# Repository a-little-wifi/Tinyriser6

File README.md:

# Tinyriser Hex (Tinyriser6)
Tinyriser for the Tiny6 and Tiny7 generation of Lenovo Tiny PCs
Same idea as [the original Tinyriser](https://github.com/a-little-wifi/Tinyriser), but for the next gen.  
Compatible with M90q gen 1 & 2, P340 and P350 Tiny (M70q and M80q don't have the riser slot populated)

## Features:

- PCIe x16 slot (8 lanes from CPU)
- M.2 M-key NVMe slot (4 lanes from PCH)
- USB 2.0 port
- Fan header
- Other random riser slot IO breakout (for science)
- Plug and play, no mainboard modification necessary

> front and back in 3D render  

> front and back in real life

This riser gives you access to the PCIe x8 link from the CPU and the PCIe x4 link from the PCH at the same time, in the form of a PCIe x16 (physical) slot and an M.2 M-key slot.  
Also has a USB 2.0 port because the riser slot has it so why not.  
It does not require any modification to the motherboard of the host machine, just plug and play.  

Using this riser, you can install a low profile PCIe card just as you can with the stock risers, and add an extra M.2 NVMe SSD in addition to the onboard ones. The SSD is tucked away near the front of the machine, plugged into a right angle M-key M.2 slot that holds the SSD firmly in place.  
M.2 2280 length SSDs might have some trouble fitting, especially in combination with longer PCIe cards as they run into the fan and speaker connector on the motherboard. I leave it up to the individual to judge what will be a good fit.  

I've successfully tested this design in P340 (Tiny6) and P350 (Tiny7) machines. Both PCIe links with all lanes as well as the USB port are fully functional in both of them.  

> riser installed in a P340 with PCIe card, SSD and USB cable attached

### Fan header:
The fan header has the same 3 modes as on the original Tinyriser:
- 12V no PWM
- 12V with PWM
- Voltage controlled speed

The last 2 modes require some kind of fan controller module plugged into the provided header. This has not been designed yet, but the possibility exists.

**Update: v1.1 now has a '5V no PWM' mode available as well, adding an extra jumper from the 5V rail instead of the 12V rail. This 5V rail is always on though, so the fan would be powered even when the system is turned off.**  
**Also be careful when soldering the 5V jumper, it's really close to a 12V pin from the PCIe slot.**

## Thank you

I want to say thank you to everyone for the kind words about my first riser design, I never expected it to reach so far and get so much interest. I originally made it just because I wanted to know if it would work and because I needed a riser for my M720q anyway (would you believe I don't own or have even ever seen a stock Lenovo Tiny5 riser?).  
The experience has had its ups and downs, it turned out I was nowhere near prepared to be handling sales, there's been a few people trying to take credit for my work, and life has been throwing one thing after the other at me, there've been many times I felt bad about it (sorry for the occasional blunt or delayed replies), but in the end I'm still glad I could put it out there and that people have been able to enjoy it. I've even had people reach out suggesting different riser versions and requesting assistance with making modified designs, that's what I love to see. I hope the same will go for this one.

So really, thank you to everyone who has expressed their appreciation for my work, and maybe even bought one from me directly during the short time that was possible. Your support really fills my little wifi heart with motivation to continue making my silly pieces of PCB art in my own way. I hope to keep delving into the depths of modern PC hardware architecture and to deliver more high quality designs with some soul of their own in the future.

This design is the result of everything I've learned from my experience with the original Tinyariser and more. It includes an improved edge connector design that better follows industry standards, a short-circuit discouragement pictogram, several hidden cats, silly puns and more magic.

### Made with ❤ and ✨ by Wifi. I poured my heart, soul and passion into this, I hope you love it too!

## Parts list: 
| part                    | model                     | link                                                                                             |
|-------------------------|---------------------------|--------------------------------------------------------------------------------------------------|
| PCIe slot               | UMAX 3183-10203P1T        | https://www.lcsc.com/product-detail/Card-Edge-Connectors_UMAX-3183-10203P1T_C404116.html         |
| Vertical M-key slot     | HOAUC HYCW19M-05NGFF-530B | https://www.lcsc.com/product-detail/C41430861.html                                               |
| Alt Vertical M-key slot | Lotes APCI0110-P001A      | (available on aliexpress)                                                                        |
| Screwpost               | YIYUAN SMTSOM340BTR       | https://www.lcsc.com/product-detail/Other-nuts_YIYUAN-SMTSOM340BTR_C5301786.html                 |
| USB port                | Jing 906-862A1118D10200   | https://www.lcsc.com/product-detail/C2763236.html (Warning: EasyEDA footprint pinout is reversed)|

## JLC PCB ordering details:

Please use the files from the v1 release, the main repo might be in the middle of version changes

You're welcome to place your own group orders if you know enough people who are interested in getting one of these risers, however please leave actual selling of this riser design to me and people I've specifically made agreements with.

### Order it in purple Ò̶̖͗̅Ŕ̵͈ ̴̠̬̝̚E̷̖̘̐́̿L̴̢͉̠̕͝S̵͖̺̰̋̀Ē̶̫̾ͅ

> Screenshot of the JLC PCB order settings used for Tinyriser6

# Attribution
If you distribute this design or use this design to create a derivative design, you must keep attribution to this original design, in addition to following the terms in the license

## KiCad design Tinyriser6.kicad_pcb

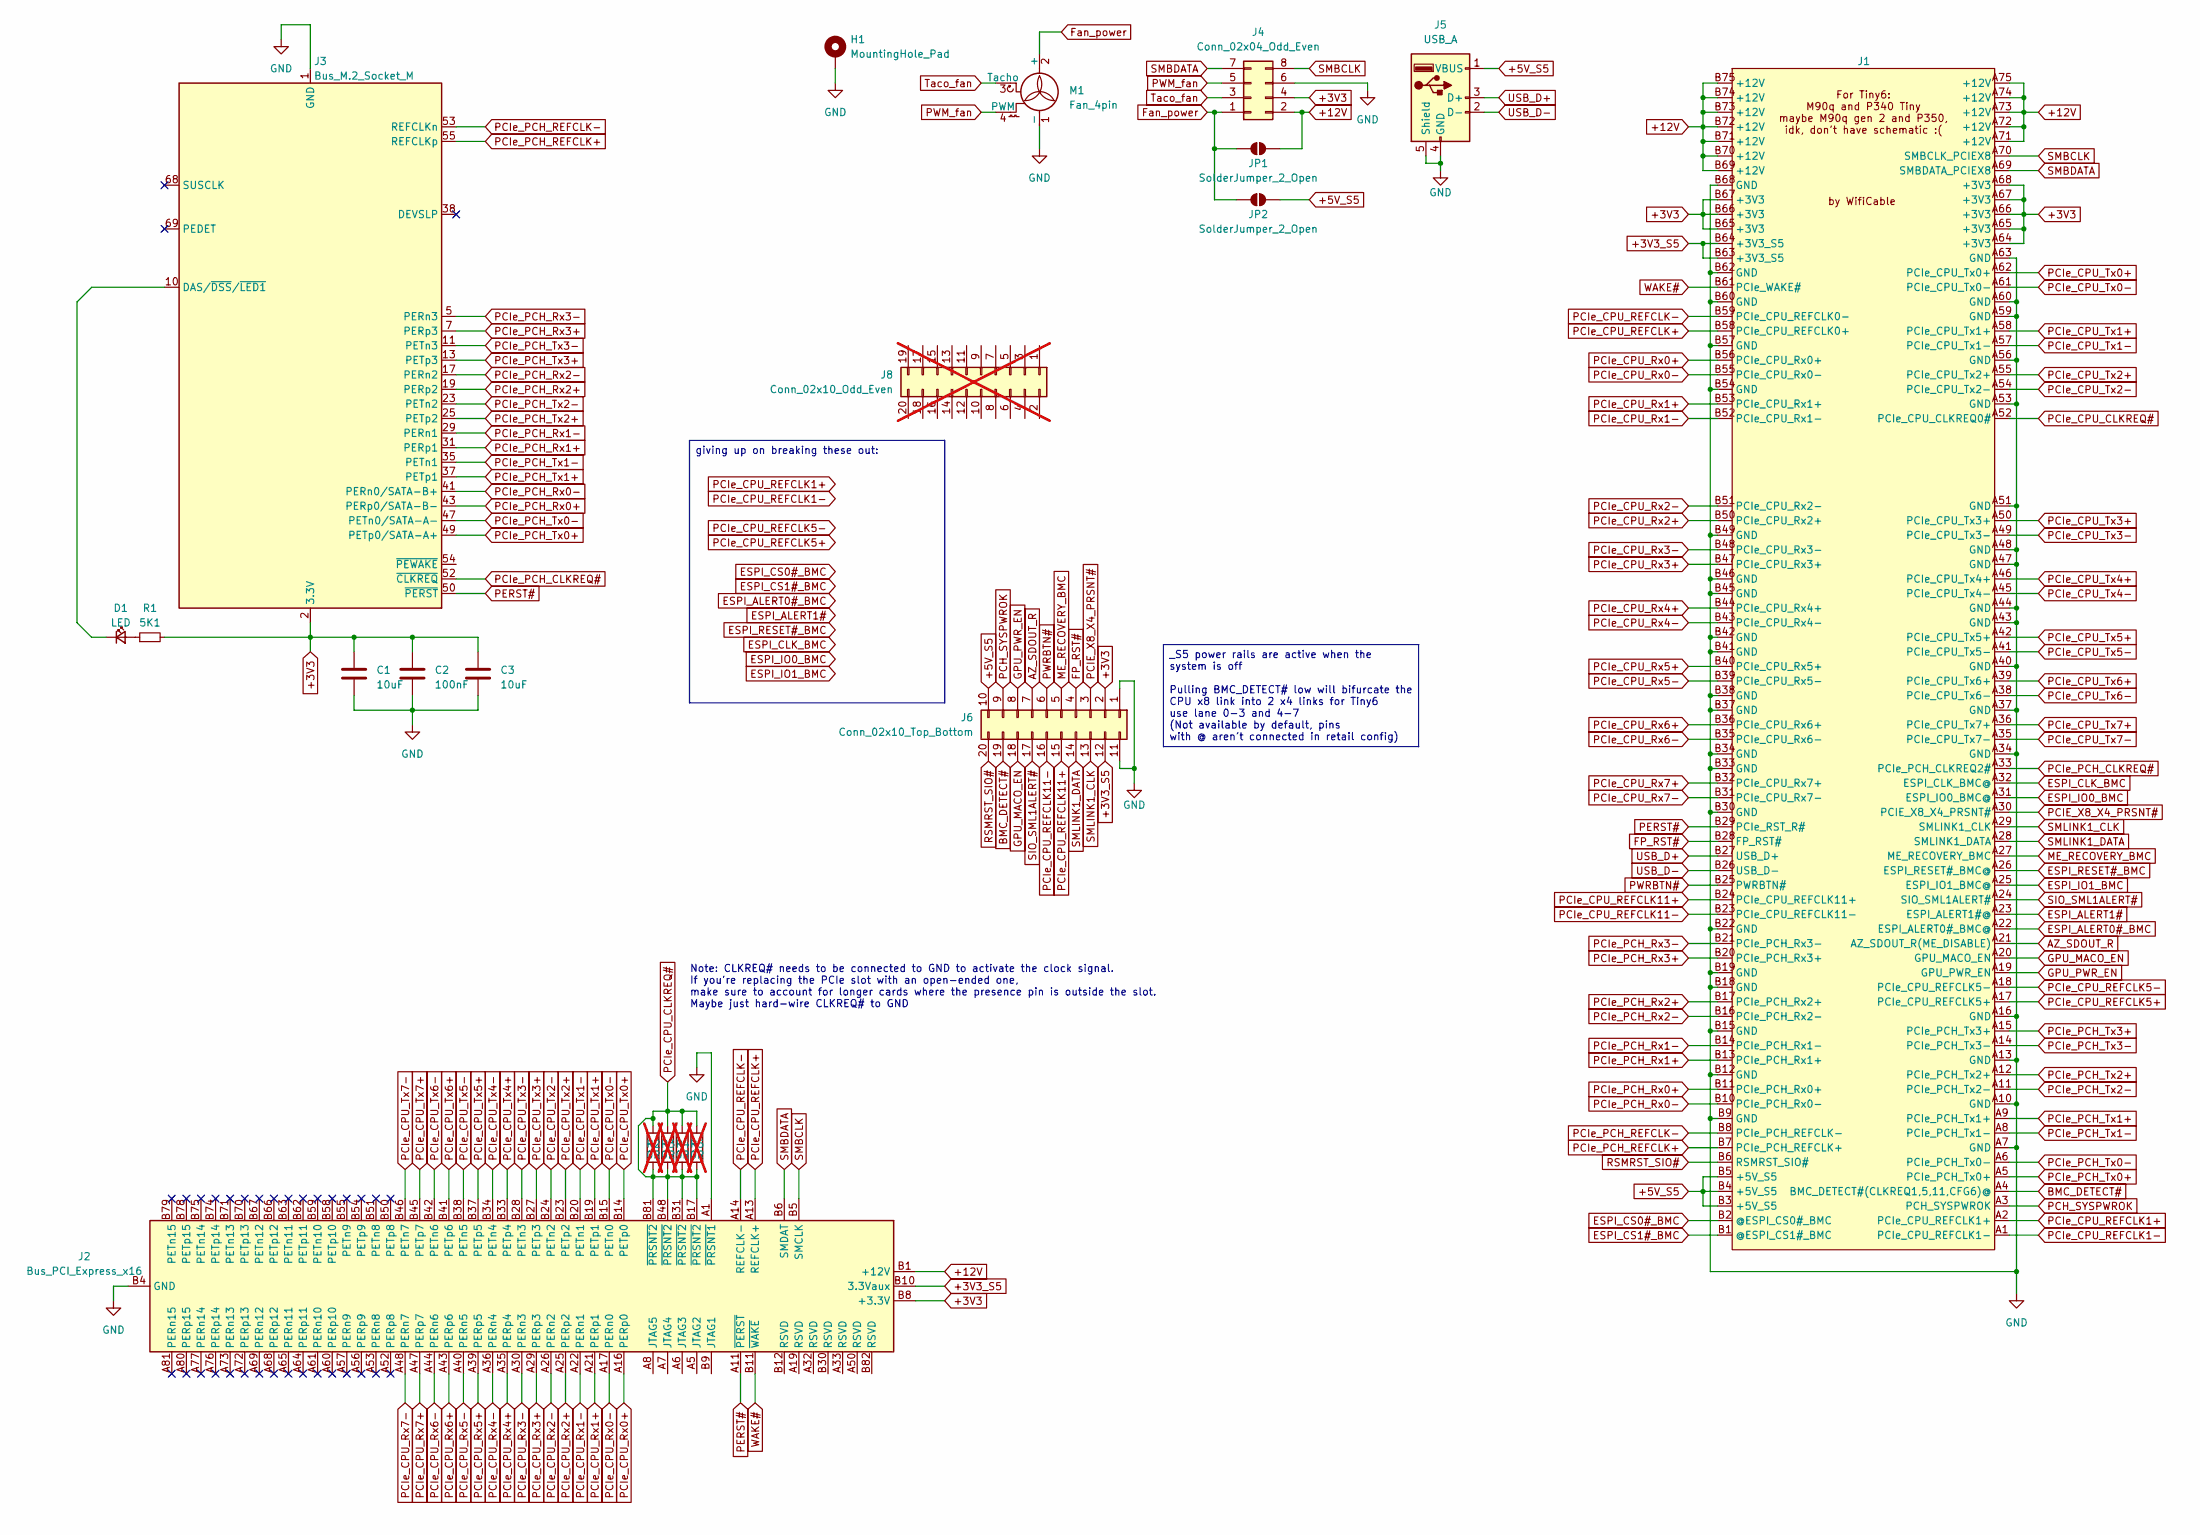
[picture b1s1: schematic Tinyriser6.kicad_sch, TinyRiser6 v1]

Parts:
C1, C3: 10uF; C_0603_1608Metric
C2: 100nF; C_0603_1608Metric
D1: LED; D_0603_1608Metric_Pad1.05x0.95mm_HandSolder
H1: MountingHole_Pad; MountingHole_4.3mm_M4_ISO7380_Pad_TopOnly
J1: TinyRiser6
J2: Bus_PCI_Express_x16; PCIe_x16_tht_smallholes
J3: Bus_M.2_Socket_M; M.2_NGFF_KeyM_H5.3_Vertical
J4: Conn_02x04_Odd_Even; PinSocket_2x04_P2.54mm_Horizontal
J5: USB_A; that-sideways-usb
J6: Conn_02x10_Top_Bottom; PinHeader_2x10_P2.54mm_Vertical
J8: Conn_02x10_Odd_Even; PinHeader_2x10_P2.54mm_Vertical; not fitted
JP1, JP2: SolderJumper_2_Open; SolderJumper-2_P1.3mm_Open_TrianglePad1.0x1.5mm
M1: Fan_4pin; PinHeader_1x04_P2.54mm_Horizontal
R1: 5K1; R_0603_1608Metric_Pad0.98x0.95mm_HandSolder
R2, R3, R4, R5: 0R; R_0603_1608Metric_Pad0.98x0.95mm_HandSolder; not fitted

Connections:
+3V3: C1.1, C2.1, C3.1, J1.A64 (+3V3), J1.A65 (+3V3), J1.A66 (+3V3), J1.A67 (+3V3), J1.A68 (+3V3), J1.B65 (+3V3), J1.B66 (+3V3), J1.B67 (+3V3), J2.A9 (+3.3V), J2.A10 (+3.3V), J2.B8 (+3.3V), J3.2 (3.3V), J3.4 (3.3V), J3.12 (3.3V), J3.14 (3.3V), J3.16 (3.3V), J3.18 (3.3V), J3.70 (3.3V), J3.72 (3.3V), J3.74 (3.3V), J4.4, J6.2, R1.2
+3V3_S5: J1.B63 (+3V3_S5), J1.B64 (+3V3_S5), J2.B10 (3.3Vaux), J6.12
+5V_S5: J1.B3 (+5V_S5), J1.B4 (+5V_S5), J1.B5 (+5V_S5), J5.1 (VBUS), J6.10, JP2.2 (B)
+12V: J1.A71 (+12V), J1.A72 (+12V), J1.A73 (+12V), J1.A74 (+12V), J1.A75 (+12V), J1.B69 (+12V), J1.B70 (+12V), J1.B71 (+12V), J1.B72 (+12V), J1.B73 (+12V), J1.B74 (+12V), J1.B75 (+12V), J2.A2 (+12V), J2.A3 (+12V), J2.B1 (+12V), J2.B2 (+12V), J2.B3 (+12V), J4.2, JP1.2 (B)
AZ_SDOUT_R: J1.A21 (AZ_SDOUT_R(ME_DISABLE)), J6.7
BMC_DETECT#: J1.A4 (BMC_DETECT#(CLKREQ1,5,11,CFG6)@), J6.19
ESPI_ALERT0#_BMC: J1.A22 (ESPI_ALERT0#_BMC@)
ESPI_ALERT1#: J1.A23 (ESPI_ALERT1#@)
ESPI_CLK_BMC: J1.A32 (ESPI_CLK_BMC@)
ESPI_CS0#_BMC: J1.B2 (@ESPI_CS0#_BMC)
ESPI_CS1#_BMC: J1.B1 (@ESPI_CS1#_BMC)
ESPI_IO0_BMC: J1.A31 (ESPI_IO0_BMC@)
ESPI_IO1_BMC: J1.A25 (ESPI_IO1_BMC@)
ESPI_RESET#_BMC: J1.A26 (ESPI_RESET#_BMC@)
FP_RST#: J1.B28 (FP_RST#), J6.4
Fan_power: J4.1, JP1.1 (A), JP2.1 (A), M1.2 (+)
GND: C1.2, C2.2, C3.2, H1.1, J1.A7 (GND), J1.A10 (GND), J1.A13 (GND), J1.A16 (GND), J1.A34 (GND), J1.A37 (GND), J1.A40 (GND), J1.A43 (GND), J1.A44 (GND), J1.A47 (GND), J1.A48 (GND), J1.A51 (GND), J1.A53 (GND), J1.A56 (GND), J1.A59 (GND), J1.A60 (GND), J1.A63 (GND), J1.B9 (GND), J1.B12 (GND), J1.B15 (GND), J1.B18 (GND), J1.B19 (GND), J1.B22 (GND), J1.B30 (GND), J1.B33 (GND), J1.B34 (GND), J1.B37 (GND), J1.B38 (GND), J1.B41 (GND), J1.B42 (GND), J1.B45 (GND), J1.B46 (GND), J1.B49 (GND), J1.B54 (GND), J1.B57 (GND), J1.B60 (GND), J1.B62 (GND), J1.B68 (GND), J2.A1 (~PRSNT1), J2.A4 (GND), J2.A12 (GND), J2.A15 (GND), J2.A18 (GND), J2.A20 (GND), J2.A23 (GND), J2.A24 (GND), J2.A27 (GND), J2.A28 (GND), J2.A31 (GND), J2.A34 (GND), J2.A37 (GND), J2.A38 (GND), J2.A41 (GND), J2.A42 (GND), J2.A45 (GND), J2.A46 (GND), J2.A49 (GND), J2.A51 (GND), J2.A54 (GND), J2.A55 (GND), J2.A58 (GND), J2.A59 (GND), J2.A62 (GND), J2.A63 (GND), J2.A66 (GND), J2.A67 (GND), J2.A70 (GND), J2.A71 (GND), J2.A74 (GND), J2.A75 (GND), J2.A78 (GND), J2.A79 (GND), J2.A82 (GND), J2.B4 (GND), J2.B7 (GND), J2.B13 (GND), J2.B16 (GND), J2.B18 (GND), J2.B21 (GND), J2.B22 (GND), J2.B25 (GND), J2.B26 (GND), J2.B29 (GND), J2.B32 (GND), J2.B35 (GND), J2.B36 (GND), J2.B39 (GND), J2.B40 (GND), J2.B43 (GND), J2.B44 (GND), J2.B47 (GND), J2.B49 (GND), J2.B52 (GND), J2.B53 (GND), J2.B56 (GND), J2.B57 (GND), J2.B60 (GND), J2.B61 (GND), J2.B64 (GND), J2.B65 (GND), J2.B68 (GND), J2.B69 (GND), J2.B72 (GND), J2.B73 (GND), J2.B76 (GND), J2.B77 (GND), J2.B80 (GND), J3.1 (GND), J3.3 (GND), J3.9 (GND), J3.15 (GND), J3.21 (GND), J3.27 (GND), J3.33 (GND), J3.39 (GND), J3.45 (GND), J3.51 (GND), J3.57 (GND), J3.71 (GND), J3.73 (GND), J3.75 (GND), J4.6, J5.4 (GND), J5.5 (Shield), J6.1, J6.11, M1.1 (-)
GPU_MACO_EN: J1.A20 (GPU_MACO_EN), J6.18
GPU_PWR_EN: J1.A19 (GPU_PWR_EN), J6.8
ME_RECOVERY_BMC: J1.A27 (ME_RECOVERY_BMC), J6.5
unnamed: D1.2 (A), R1.1
unnamed: D1.1 (K), J3.10 (DAS/~DSS/~LED1)
PCH_SYSPWROK: J1.A3 (PCH_SYSPWROK), J6.9
PCIE_X8_X4_PRSNT#: J1.A30 (PCIE_X8_X4_PRSNT#), J6.3
PCIe_CPU_CLKREQ#: J1.A52 (PCIe_CPU_CLKREQ0#), J2.B17 (~PRSNT2), J2.B31 (~PRSNT2), J2.B48 (~PRSNT2), J2.B81 (~PRSNT2), R2.1, R2.2, R3.1, R3.2, R4.1, R4.2, R5.1, R5.2
PCIe_CPU_REFCLK1+: J1.A2 (PCIe_CPU_REFCLK1+)
PCIe_CPU_REFCLK1-: J1.A1 (PCIe_CPU_REFCLK1-)
PCIe_CPU_REFCLK5+: J1.A17 (PCIe_CPU_REFCLK5+)
PCIe_CPU_REFCLK5-: J1.A18 (PCIe_CPU_REFCLK5-)
PCIe_CPU_REFCLK11+: J1.B24 (PCIe_CPU_REFCLK11+), J6.15
PCIe_CPU_REFCLK11-: J1.B23 (PCIe_CPU_REFCLK11-), J6.16
PCIe_CPU_REFCLK+: J1.B58 (PCIe_CPU_REFCLK0+), J2.A13 (REFCLK+)
PCIe_CPU_REFCLK-: J1.B59 (PCIe_CPU_REFCLK0-), J2.A14 (REFCLK-)
PCIe_CPU_Rx0+: J1.B56 (PCIe_CPU_Rx0+), J2.A16 (PERp0)
PCIe_CPU_Rx0-: J1.B55 (PCIe_CPU_Rx0-), J2.A17 (PERn0)
PCIe_CPU_Rx1+: J1.B53 (PCIe_CPU_Rx1+), J2.A21 (PERp1)
PCIe_CPU_Rx1-: J1.B52 (PCIe_CPU_Rx1-), J2.A22 (PERn1)
PCIe_CPU_Rx2+: J1.B50 (PCIe_CPU_Rx2+), J2.A25 (PERp2)
PCIe_CPU_Rx2-: J1.B51 (PCIe_CPU_Rx2-), J2.A26 (PERn2)
PCIe_CPU_Rx3+: J1.B47 (PCIe_CPU_Rx3+), J2.A29 (PERp3)
PCIe_CPU_Rx3-: J1.B48 (PCIe_CPU_Rx3-), J2.A30 (PERn3)
PCIe_CPU_Rx4+: J1.B44 (PCIe_CPU_Rx4+), J2.A35 (PERp4)
PCIe_CPU_Rx4-: J1.B43 (PCIe_CPU_Rx4-), J2.A36 (PERn4)
PCIe_CPU_Rx5+: J1.B40 (PCIe_CPU_Rx5+), J2.A39 (PERp5)
PCIe_CPU_Rx5-: J1.B39 (PCIe_CPU_Rx5-), J2.A40 (PERn5)
PCIe_CPU_Rx6+: J1.B36 (PCIe_CPU_Rx6+), J2.A43 (PERp6)
PCIe_CPU_Rx6-: J1.B35 (PCIe_CPU_Rx6-), J2.A44 (PERn6)
PCIe_CPU_Rx7+: J1.B32 (PCIe_CPU_Rx7+), J2.A47 (PERp7)
PCIe_CPU_Rx7-: J1.B31 (PCIe_CPU_Rx7-), J2.A48 (PERn7)
PCIe_CPU_Tx0+: J1.A62 (PCIe_CPU_Tx0+), J2.B14 (PETp0)
PCIe_CPU_Tx0-: J1.A61 (PCIe_CPU_Tx0-), J2.B15 (PETn0)
PCIe_CPU_Tx1+: J1.A58 (PCIe_CPU_Tx1+), J2.B19 (PETp1)
PCIe_CPU_Tx1-: J1.A57 (PCIe_CPU_Tx1-), J2.B20 (PETn1)
PCIe_CPU_Tx2+: J1.A55 (PCIe_CPU_Tx2+), J2.B23 (PETp2)
PCIe_CPU_Tx2-: J1.A54 (PCIe_CPU_Tx2-), J2.B24 (PETn2)
PCIe_CPU_Tx3+: J1.A50 (PCIe_CPU_Tx3+), J2.B27 (PETp3)
PCIe_CPU_Tx3-: J1.A49 (PCIe_CPU_Tx3-), J2.B28 (PETn3)
PCIe_CPU_Tx4+: J1.A46 (PCIe_CPU_Tx4+), J2.B33 (PETp4)
PCIe_CPU_Tx4-: J1.A45 (PCIe_CPU_Tx4-), J2.B34 (PETn4)
PCIe_CPU_Tx5+: J1.A42 (PCIe_CPU_Tx5+), J2.B37 (PETp5)
PCIe_CPU_Tx5-: J1.A41 (PCIe_CPU_Tx5-), J2.B38 (PETn5)
PCIe_CPU_Tx6+: J1.A39 (PCIe_CPU_Tx6+), J2.B41 (PETp6)
PCIe_CPU_Tx6-: J1.A38 (PCIe_CPU_Tx6-), J2.B42 (PETn6)
PCIe_CPU_Tx7+: J1.A36 (PCIe_CPU_Tx7+), J2.B45 (PETp7)
PCIe_CPU_Tx7-: J1.A35 (PCIe_CPU_Tx7-), J2.B46 (PETn7)
PCIe_PCH_CLKREQ#: J1.A33 (PCIe_PCH_CLKREQ2#), J3.52 (~CLKREQ)
PCIe_PCH_REFCLK+: J1.B7 (PCIe_PCH_REFCLK+), J3.55 (REFCLKp)
PCIe_PCH_REFCLK-: J1.B8 (PCIe_PCH_REFCLK-), J3.53 (REFCLKn)
PCIe_PCH_Rx0+: J1.B11 (PCIe_PCH_Rx0+), J3.43 (PERp0/SATA-B-)
PCIe_PCH_Rx0-: J1.B10 (PCIe_PCH_Rx0-), J3.41 (PERn0/SATA-B+)
PCIe_PCH_Rx1+: J1.B13 (PCIe_PCH_Rx1+), J3.31 (PERp1)
PCIe_PCH_Rx1-: J1.B14 (PCIe_PCH_Rx1-), J3.29 (PERn1)
PCIe_PCH_Rx2+: J1.B17 (PCIe_PCH_Rx2+), J3.19 (PERp2)
PCIe_PCH_Rx2-: J1.B16 (PCIe_PCH_Rx2-), J3.17 (PERn2)
PCIe_PCH_Rx3+: J1.B20 (PCIe_PCH_Rx3+), J3.7 (PERp3)
PCIe_PCH_Rx3-: J1.B21 (PCIe_PCH_Rx3-), J3.5 (PERn3)
PCIe_PCH_Tx0+: J1.A5 (PCIe_PCH_Tx0+), J3.49 (PETp0/SATA-A+)
PCIe_PCH_Tx0-: J1.A6 (PCIe_PCH_Tx0-), J3.47 (PETn0/SATA-A-)
PCIe_PCH_Tx1+: J1.A9 (PCIe_PCH_Tx1+), J3.37 (PETp1)
PCIe_PCH_Tx1-: J1.A8 (PCIe_PCH_Tx1-), J3.35 (PETn1)
PCIe_PCH_Tx2+: J1.A12 (PCIe_PCH_Tx2+), J3.25 (PETp2)
PCIe_PCH_Tx2-: J1.A11 (PCIe_PCH_Tx2-), J3.23 (PETn2)
PCIe_PCH_Tx3+: J1.A15 (PCIe_PCH_Tx3+), J3.13 (PETp3)
PCIe_PCH_Tx3-: J1.A14 (PCIe_PCH_Tx3-), J3.11 (PETn3)
PERST#: J1.B29 (PCIe_RST_R#), J2.A11 (~PERST), J3.50 (~PERST)
PWM_fan: J4.5, M1.4 (PWM)
PWRBTN#: J1.B25 (PWRBTN#), J6.6
RSMRST_SIO#: J1.B6 (RSMRST_SIO#), J6.20
SIO_SML1ALERT#: J1.A24 (SIO_SML1ALERT#), J6.17
SMBCLK: J1.A70 (SMBCLK_PCIEX8), J2.B5 (SMCLK), J4.8
SMBDATA: J1.A69 (SMBDATA_PCIEX8), J2.B6 (SMDAT), J4.7
SMLINK1_CLK: J1.A29 (SMLINK1_CLK), J6.13
SMLINK1_DATA: J1.A28 (SMLINK1_DATA), J6.14
Taco_fan: J4.3, M1.3 (Tacho)
USB_D+: J1.B27 (USB_D+), J5.3 (D+)
USB_D-: J1.B26 (USB_D-), J5.2 (D-)
WAKE#: J1.B61 (PCIe_WAKE#), J2.B11 (~WAKE)

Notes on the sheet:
Note: CLKREQ# needs to be connected to GND to activate the clock signal. If you're replacing the PCIe slot with an open-ended one, make sure to account for longer cards where the presence pin is outside the slot. Maybe just hard-wire CLKREQ# to GND
_S5 power rails are active when the system is off Pulling BMC_DETECT# low will bifurcate the CPU x8 link into 2 x4 links for Tiny6 use lane 0-3 and 4-7 (Not available by default, pins with @ aren't connected in retail config)
giving up on breaking these out:

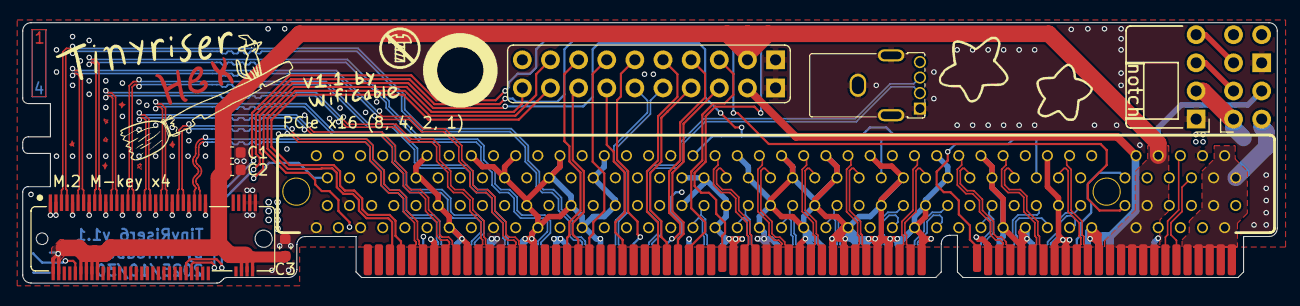
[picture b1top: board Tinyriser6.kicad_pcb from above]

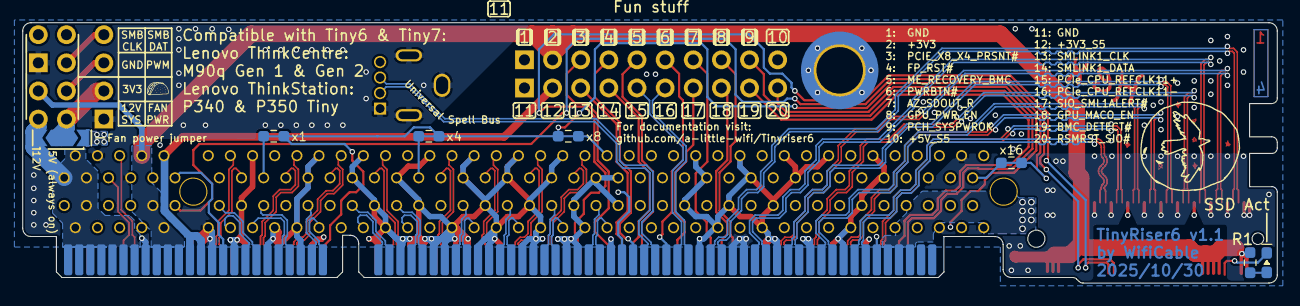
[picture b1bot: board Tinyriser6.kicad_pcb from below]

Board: 4 copper layers, 113.2 x 23.5 mm, 19 parts (9 on the bottom side), 85 nets.

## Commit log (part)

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2024-03-05 Added description to readme
2024-07-07 Imported a bunch of verified changes from Tiny5 riser v2
2024-08-05 Updated riser slot info with bifurcation possibility
2024-11-29 Temporarily adding TinyRiser8 symbol for transfer
2025-02-22 carrying over a bunch of stuff from original tinyriser
2025-02-28 found one more tiny8 pin from beefy riser
2025-03-01 slightly adjusted edge connector footprint dimensions
2025-03-08 started breaking out all the weird pins
2025-03-08 Added random io header, usb and started routing M.2 PCIe
2025-03-08 Finished routing M.2 PCIe lanes
2025-03-08 routed power and some misc signals
2025-03-08 wired up fan header
2025-03-08 routed M.2 power
2025-03-08 little adjustments
2025-03-12 Trying to figure out what to do with the random io
2025-03-15 changed usb port, testing new logo placement
2025-03-16 giving up on some random IO pins
2025-03-16 added todo list
2025-03-16 Moved PCIe slot down 0.25mm
2025-03-16 wired up ssd led
2025-03-16 nudged some lanes
2025-03-16 Adjusted compatibility text
2025-03-16 changed resistor refdes
2025-03-16 giving up on breaking out ESPI, tuned some diffpairs
2025-03-16 Changed misc IO header to 2x10 and started routing it
2025-03-16 routed misc m.2 signals and mostly routed misc IO header
2025-03-16 made misc IO traces prettier
2025-03-16 routed misc io header power pins
2025-03-17 Added fill to break out 5V
2025-03-17 added m.2 slot 3d model
    probably doesn't work on anything but my laptop lol
2025-03-17 added 3d model for m.2 slot but properly this time
2025-03-17 fixed 3d model alignment
2025-03-19 finished connecting pretty much all of the random io
2025-03-19 UNROUTED 0 LETS GOOOO
    lots of tweaks left to make though :3
2025-03-20 routed 5V rail properly
2025-03-20 added ground keepout zones
2025-03-20 ran some ground, added PCH lane wiggles
2025-03-20 fixed some layer conflicts
2025-03-20 saved the fat cat
2025-03-20 bunch of little optimizations
2025-03-20 a few more vias
2025-03-20 added soldermask keepout on edge connector and clarified riser slot symbol
2025-03-20 more ground viassssss
    i wonder if it does pcie 4.0 lol (if someone can figure out how to make tiny7 do that)
2025-03-25 lil extra note
2025-03-28 adjusted keepout zone
2025-03-29 checked edge conn dimensions
2025-03-30 added more gnd vias around pcie
2025-03-31 little trace nudge
    tiny meaningless thing to commit but i gotta be able to keep the laptops in sync lol
2025-04-01 made ground fill a little prettier
2025-04-01 slight gnd via nudge to improve 3.3V rail connection
2025-04-01 added documentation note
2025-04-01 added lock files to gitignore
    should have done that ages ago lol
2025-04-04 changed usb footprint
2025-04-04 moved m.2 slot down a little and added clearance for tiny6 bios chip
2025-04-04 hid inapplicable 3d model
2025-04-04 idk lol
2025-04-06 made some diffpairs a bit nicer
    pcie 4.0 tonight queen 🥺
2025-04-07 Adjusted edge connector dimensions a bit more
    really glad i grabbed some calipers anyway, it might not have fit otherwise
2025-04-10 working on changing misc io header to 2.54mm and set m.2 slot to thermal reliefs for handsoldering
2025-04-10 Finished changing misc io header to 2.54mm?
2025-04-10 actually finished that fr this time 💯
2025-04-10 trace nudgin
2025-05-01 Improved edge connector footprint
    looooong loooong piiiiinssss
2025-05-03 wobl
2025-05-07 woblr
2025-05-07 trying interesting text stuff + bacon
2025-05-08 meow
2025-05-08 usb ground vias
2025-05-08 A few more ground vias
2025-05-08 Changed usb ground vias a little
2025-05-08 Finalized USB port
2025-05-08 bunch of minor changes
2025-05-08 Added silkscreen telling you not to put a screw directly into the pcb
    like bruh
    don't do that
    why do all of my risers keep blowing u- 💥
2025-05-08 Added silkscreen layer to protect from screw damage
2025-05-09 changed silkscreen a little
2025-05-09 unfinished attempt at putting misc io header pinout on silkscreen
2025-05-14 Changed misc io header pin numbering and added labels for pinout
2025-05-15 little silkscreen tweaks
2025-05-15 grouped some items
2025-05-16 LOGO YEAH
    I CAST DIFFERENTIAL PAIR MAGIC
2025-05-16 Todo completed, added date and little easter egg
2025-05-16 fixed a bunch of things and tweaked some silkscreen
    remember to run DRC, kids
2025-05-16 remove ribs
2025-05-16 return of the birb
2025-05-16 moved some vias out of silkscreen area
2025-05-17 Moved some more vias and traces around to avoid silkscreen
    final version fr this time 💯
2025-05-17 Updated datecode and fixed keepout clearance
2025-05-17 didn't label my schematic sheet right smh 😔
2025-05-17 Fixed some net names
2025-05-17 oop forgot to save pcb file
2025-05-17 remove balls
2025-05-21 Made logo text bigger
    final version fr this time???
2025-05-21 forgor to rerun fills 😭
    FINAL FR THIS TIME PLEASE
2025-05-21 removed bacon from edge.cuts and tested gerber export
2025-05-21 Made screwpost hole 0.1mm smaller
    This is a change from Tinyriser v2.1, not sure how it didn't end up being carried over to this one
2025-05-21 forgot to update fills again lol
2025-05-21 made silkscreen reach hole edge again
2025-05-22 Updated datecode
2025-05-23 Slight copper fill optimizations
2025-05-23 Some schematic notes
2025-05-23 Added license
2025-05-23 Added attribution note
2025-05-23 post-design-review fixes
2025-05-24 Small fill adjustments
2025-05-25 forgot to change the date again yesterday
    maybe i shouldn't put the date on the board to-the-day.... prone to messing it up lol
2025-05-28 Adjusted edge connector dimensions some more
    based on paper prototype, they should be good fr now, I did extra measurements of both the slot and an original riser
2025-05-29 extra edge connector measurements
2025-05-30 removed some leftovers
2025-05-30 Set clkreq resistors to DNP
2025-07-17 small tiny8 symbol updates
    based on official tiny8 x4 riser
2025-08-04 Removed test Tiny8 riser symbol from schematic
2025-10-27 Wrote a proper readme and added pictures
    ❤️
2025-10-27 case sensitive filenames lol
2025-10-27 little readme changes
2025-10-27 sales note
2025-10-27 moved sales note
2025-10-27 that's a feature
2025-10-27 Added pdf schematic
    now you don't need kicad just to look at schematic lol
2025-10-28 Fixed refclk number being wrong on silkscreen + updated project to KiCad 9
    How did I miss that all this time... Not worth bumping the version number over though.
2025-10-30 Some minor adjustments + added 5V option for fan header, bumped version to v1.1
    5V rail is always on though, even when the system is powered off
2025-10-30 Updated silkscreen to say v1.1
2025-10-30 improved v1.1 silkscreen spacing
2025-11-01 Added info about 5V fan mode to readme
2026-04-29 Updated parts list
    Changed lcsc available one to preferred option and updated link
